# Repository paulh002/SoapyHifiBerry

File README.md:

# SoapyHifiBerry 
The SoapyHifiBerry driver is to use the HifiBerry DAC + ADC (Pro) as a SDR Tranceiver in combination with a Tayloe detector / Mixer.
The idea and design of the detector is from the book "Software Defined Radio Tranceiver" T41-EP by AC8GY and W8TEE
I adapted the design for use with Raspberry PI 4B. On the PCB there is a Tayloe mixer FST3253 / SN74CBT3252 and a Si5351 oscilator.
A SN74HC74 is used to devide the clock by 4 and deliver 90 degree phase shift. Alternative 2 si5351 can be used clock 0 and clock 1 will deliver 90 deg phase shift. A TCA9548 is used to switch the i2c bus.
The SoapyHifiBerry driver work with my SDR software SDRBERRY https://github.com/paulh002/sdrberry, I did not test it with other SDR software and all is an experiment.
(SoapyHifiBerry relies on RtAudio library, which is included staticly. This can give problems with applications using also RtAudio but a different version, 
in that case remove the RtAudio.cpp from SoapyHifiBerry and use correct RtAudio.h)

The sdr41-rxtx board uses a Si5351A-B-GM which has 8 outputs 2 outputs are used in quadrature for receive and 2 outputs for receive. Unfortunaly 160 M is not possible in this design because of limitations of the si5351.
An option would be to add a divide by 2 chip. The board compresses the whole design to a single pcb. SoapyHifiBerry can be configured by setting the mode to IQSINGLEMULTI and the multiplier to 1.

Done:
- Support 2 times Si5351 (RX and TX)
- Si5351 I2C interface
- Gain interface
- Receive IQ signal
- Transmit IQ interface
- CMake compilation

Installation of libraries is necessary:
- Liquid DSP
- Alsa audio
- SoapySDR
- pthread

# Installation

## Install libraries

git clone https://github.com/pothosware/SoapySDR.git
cd SoapySDR
git pull origin master
mkdir build
cd build
cmake ..
make -j4
sudo make install
sudo ldconfig

cd ~
sudo apt-get install -y fftw3-dev
git clone https://github.com/jgaeddert/liquid-dsp
git checkout v1.4.0
sudo apt-get install -y automake autoconf
cd liquid-dsp
./bootstrap.sh
./configure
make -j4
sudo make install
sudo ldconfig

## Install and compile with VisualStudio and VisualGDB
Download the repository in pi home directory  
```
git clone https://github.com/paulh002/SoapyHifiBerry  
Open project in VisualStudio and compile with VisualGDB

```

## Install and compile with CMake
```
git clone https://github.com/paulh002/SoapyHifiBerry  
cd SoapyHifiBerry
mkdir build
cd build
cmake ..
make
sudo make install
```

SoapyHifiBerry will create config file HifiBerry.cfg Si5351 correction can be configured and audio adc/dac alsa device name set
```
[si5351]
correction = "50000"
mode = "single"

[sound]
device = "snd_rpi_hifiberry_dacplusadcpro"
```

To enable 2 time si5351

```
[si5351]
mode = "IQ"
```

To enable single Si5351A-B-GM
```
[si5351]
correction = "121000"
correctiontx = "132500"
rxdrive = "2"
txdrive = "4"
mode = "IQSINGLEMULTI"
multiplier = 1
disabletxoutput = "on"
```

## QSD and QSE combined board (sdr41-rxtx)

## Separate QSD and QSE boards (Kicad rx and tx v3)

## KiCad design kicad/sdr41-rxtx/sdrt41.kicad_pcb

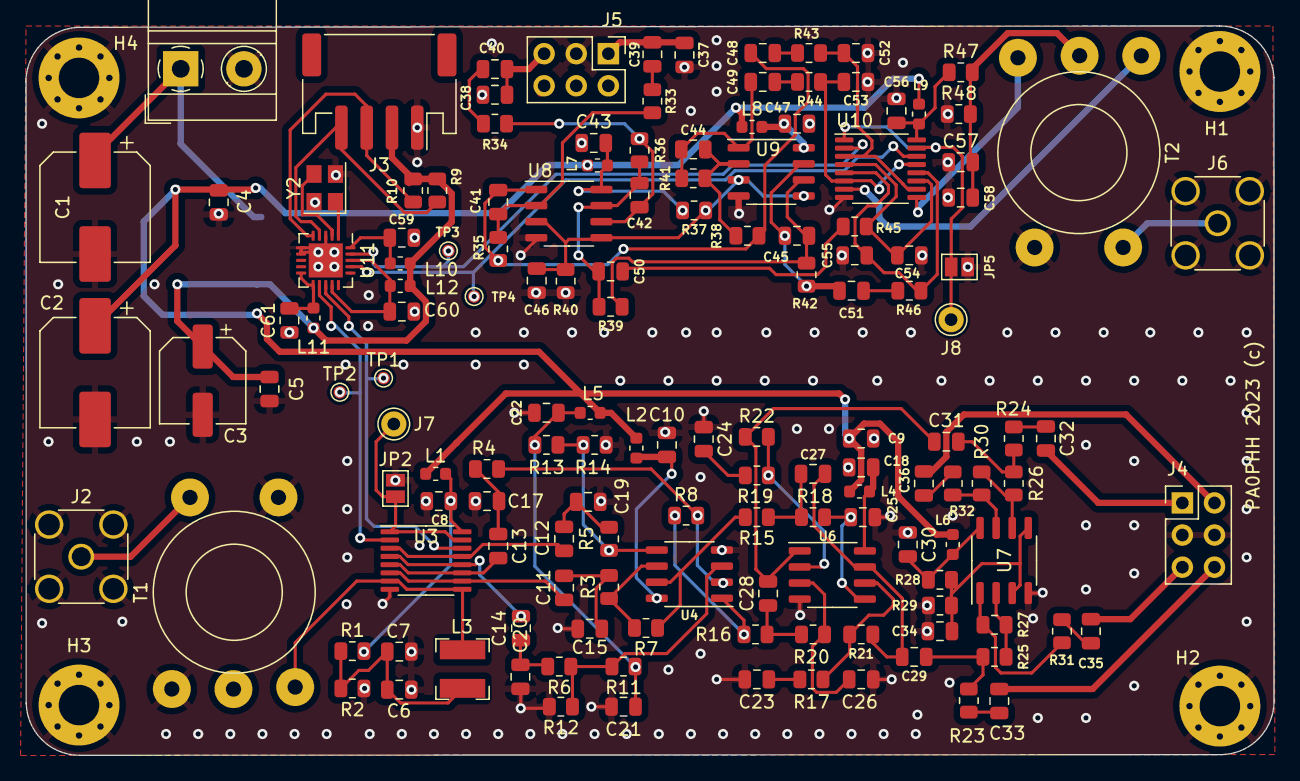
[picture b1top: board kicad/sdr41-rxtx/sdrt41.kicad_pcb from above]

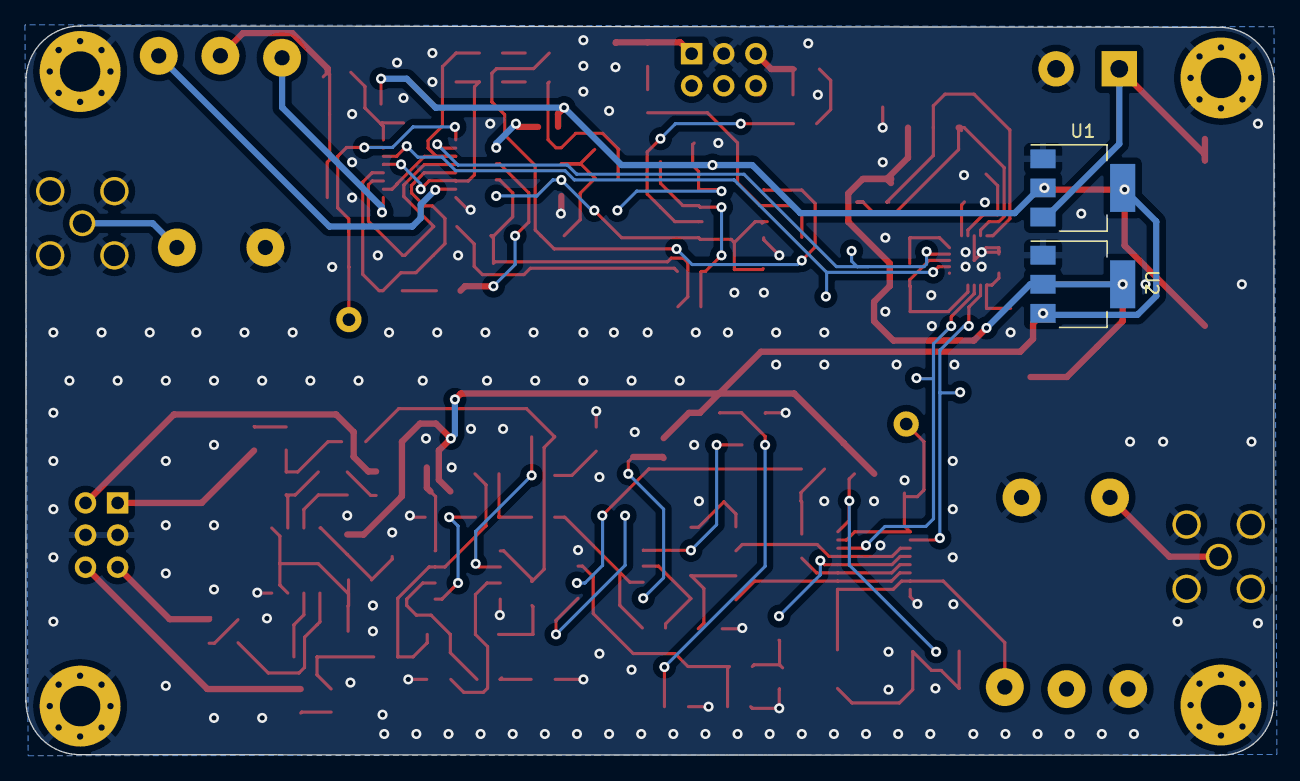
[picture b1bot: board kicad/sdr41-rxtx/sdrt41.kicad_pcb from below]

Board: 4 copper layers, 98.7 x 57.7 mm, 151 parts (2 on the bottom side), 92 nets.

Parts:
C1, C2: 100u; CP_Elec_8x10.5
C3: 47u; CP_Elec_6.3x7.7
C4, C5, C6, C8, C10, C18, C21, C22, C30, C34, C43, C47, C56, C57: 100n; C_0805_2012Metric
C7, C9, C23, C24, C29, C31, C32, C33, C35, C36, C39, C40, C46, C48, C49, C50, C51, C58, C59, C60, C61: 10u; C_0805_2012Metric
C11, C12, C13, C14: 1u; C_0805_2012Metric
C15, C17, C19, C20: 10n; C_0805_2012Metric
C25, C26, C27, C28: 68p; C_0805_2012Metric
C37, C38: 1n; C_0805_2012Metric
C41, C42, C44, C45: 100p; C_0805_2012Metric
C52, C53, C54, C55: 2n2; C_0805_2012Metric
H1, H2, H3, H4: MountingHole_Pad; MountingHole_3.2mm_M3_Pad_Via
J1: Power; TerminalBlock_MetzConnect_Type011_RT05502HBWC_1x02_P5.00mm_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
J2: Conn_Coaxial; SMA_Amphenol_132134_Vertical
J3: I2C; JST_PH_S4B-PH-SM4-TB_1x04-1MP_P2.00mm_Horizontal
J4: output; PinHeader_2x03_P2.54mm_Vertical
J5: input; PinHeader_2x03_P2.54mm_Vertical
J6: TX; SMA_Amphenol_132134_Vertical
J7: Rx; Pin_D1.0mm_L10.0mm
J8: Tx; Pin_D1.0mm_L10.0mm
JP2: RX; SolderJumper-2_P1.3mm_Open_Pad1.0x1.5mm
JP5: tx; SolderJumper-2_P1.3mm_Open_Pad1.0x1.5mm
L1, L2, L4, L5, L6, L7, L8, L9, L10, L11, L12: L; L_0603_1608Metric
L3: 100u; L_Bourns-SRN4018
R1, R2, R7, R8: 2k; R_0805_2012Metric
R3, R4, R5, R6, R23, R24, R31, R32: 100; R_0805_2012Metric
R9, R10, R37, R40, R47, R48: 2k2; R_0805_2012Metric
R11, R12, R13, R14, R28, R29, R33, R34, R35, R36, R38, R39, R41, R42: 10k; R_0805_2012Metric
R15, R16, R17, R18, R19, R20, R21, R22, R27, R30: 5.1k; R_0805_2012Metric
R25, R26: 5k1; R_0805_2012Metric
R43, R44, R45, R46: 50; R_0805_2012Metric
T1: 1:4; Transformer_Toroid_Horizontal_D12.5mm_Amidon-T44
T2: 4:1; Transformer_Toroid_Horizontal_D12.5mm_Amidon-T44
TP1: Tp1; TestPoint_Pad_D1.0mm
TP2: Tp2; TestPoint_Pad_D1.0mm
TP3: Tp3; TestPoint_Pad_D1.0mm
TP4: Tp4; TestPoint_Pad_D1.0mm
U1: LM1117-5.0; SOT-223-3_TabPin2
U2: LM1117-3.3; SOT-223-3_TabPin2
U3, U10: SN74CBT3253; TSSOP-16_4.4x5mm_P0.65mm
U4, U6, U7, U8, U9: MC33078; SO-8_3.9x4.9mm_P1.27mm
U11: Si5351A-B-GM; QFN-20-1EP_4x4mm_P0.5mm_EP2.7x2.7mm
Y2: 25 Mhz; Crystal_SMD_3225-4Pin_3.2x2.5mm

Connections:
+3V3: C3.1, C5.2, J3.2, L10.1, L11.1, L12.1, R9.1, R10.1, U2.2 (VO)
+5V: C2.1, C4.2, C9.1, L1.1, L2.1, L4.1, L5.1, L6.1, L7.1, L8.1, L9.1, U1.2 (VO), U2.3 (VI)
+12C: C10.2, L2.2, U4.8 (V+)
+12P: C18.2, L4.2, U6.8 (V+)
+12V: C1.1, J1.1, U1.3 (VI)
/I+: C33.2, J4.6
/I-: C35.1, J4.5
/Q+: C32.2, J4.1
/Q-: C36.2, J4.2
/QSE/I-tx: C37.2, C39.1, J5.1
/QSE/Q-tx: C38.2, C40.1, J5.5
Clock1: TP1.1, U3.14 (S0), U11.13 (CLK0)
Clock2: TP2.1, U3.2 (S1), U11.12 (CLK1)
Clock3: TP3.1, U10.2 (S1), U11.19 (CLK4)
Clock4: TP4.1, U10.14 (S0), U11.17 (CLK5)
GND: C1.2, C2.2, C3.2, C4.1, C5.1, C6.1, C7.1, C8.1, C9.2, C10.1, C15.1, C17.1, C18.1, C19.1, C20.1, C21.1, C22.1, C23.1, C24.1, C25.1, C26.1, C30.1, C34.1, C37.1, C38.1, C43.1, C46.1, C47.1, C52.1, C53.1, C54.1, C55.1, C56.1, C57.1, C58.1, C59.1, C60.1, C61.1, H1.1, H2.1, H3.1, H4.1, J1.2, J2.2 (Ext), J3.1, J4.3, J4.4, J5.3, J6.2 (Ext), JP2.1 (A), JP5.1 (A), R2.2, R12.2, R14.2, R29.2, R40.1, R48.1, T1.1 (AA), T1.3 (SA), T2.1 (AA), U1.1 (GND), U2.1 (GND), U3.8 (GND), U4.4 (V-), U6.4 (V-), U7.4 (V-), U8.4 (V-), U9.4 (V-), U10.8 (GND), U11.3 (A0), U11.6 (SSEN), U11.7 (OEB), U11.21 (GND), Y2.2, Y2.4
unnamed: C6.2, C7.2, L3.2, R1.1, R2.1
unnamed: C11.1, C15.2, R3.2
unnamed: C12.1, C19.2, R5.2
unnamed: C13.1, C17.2, R4.2
unnamed: C14.1, C20.2, R6.2
unnamed: C21.2, C22.2, L5.2, R11.1, R13.1
unnamed: C23.2, R17.1
unnamed: C24.2, R19.1
unnamed: C27.1, R15.1, R18.2
unnamed: C27.2, C29.1, R21.1, U6.7
unnamed: C28.1, R16.1, R20.2
unnamed: C28.2, C31.1, R22.1, U6.1
unnamed: C29.2, R23.2, R25.2
unnamed: C31.2, R24.2, R26.2
unnamed: C32.1, R24.1
unnamed: C33.1, R23.1
unnamed: C35.2, R31.1
unnamed: C36.1, R32.1
unnamed: C39.2, R33.1
unnamed: C40.2, R34.1
unnamed: C41.1, C48.1, R35.2, R38.1, U8.1
unnamed: C42.1, C50.1, R36.2, R39.1, U8.7
unnamed: C44.1, C49.1, R41.2, U9.1
unnamed: C45.1, C51.1, R42.2, U9.7
unnamed: C48.2, R43.1
unnamed: C49.2, R44.1
unnamed: C50.2, R45.1
unnamed: C51.2, R46.1
unnamed: J2.1 (In), T1.2 (AB)
unnamed: J6.1 (In), T2.2 (AB)
unnamed: J7.1, JP2.2 (B), U3.1 (1~OE), U3.15 (2~OE)
unnamed: J8.1, JP5.2 (B), U10.1 (1~OE), U10.15 (2~OE)
unnamed: R7.1, R15.2, U4.7
unnamed: R8.1, R16.2, U4.1
unnamed: R27.1, R31.2, U7.1
unnamed: R30.1, R32.2, U7.7
unnamed: L3.1, T1.5 (SB), U3.7 (1A), U3.9 (2A)
unnamed: T2.3 (SA), U10.7 (1A)
unnamed: T2.5 (SB), U10.9 (2A)
unnamed: C57.2, C58.2, R47.2, R48.2, T2.4 (SC)
unnamed: C11.2, U3.6 (1B1), U3.10 (2B1)
unnamed: C13.2, U3.5 (1B2), U3.11 (2B2)
unnamed: C14.2, U3.4 (1B3), U3.12 (2B3)
unnamed: C12.2, U3.3 (1B4), U3.13 (2B4)
unnamed: C8.2, L1.2, R1.2, U3.16 (VCC)
unnamed: R6.1, R11.2, R12.1, U4.3 (+)
unnamed: R4.1, R8.2, U4.2 (-)
unnamed: R5.1, R13.2, R14.1, U4.5 (+)
unnamed: R3.1, R7.2, U4.6 (-)
unnamed: C26.2, R20.1, U6.3 (+)
unnamed: R19.2, R22.2, U6.2 (-)
unnamed: C25.2, R18.1, U6.5 (+)
unnamed: R17.2, R21.2, U6.6 (-)
unnamed: R25.1, R27.2, U7.2 (-)
unnamed: R26.1, R30.2, U7.6 (-)
unnamed: C30.2, L6.2, R28.1, U7.8 (V+)
unnamed: C46.2, R37.2, R40.2, U8.3 (+), U8.5 (+), U9.3 (+), U9.5 (+)
unnamed: C41.2, R33.2, R35.1, U8.2 (-)
unnamed: C42.2, R34.2, R36.1, U8.6 (-)
unnamed: C43.2, L7.2, R37.1, U8.8 (V+)
unnamed: C44.2, R38.2, R41.1, U9.2 (-)
unnamed: C45.2, R39.2, R42.1, U9.6 (-)
unnamed: C47.2, L8.2, U9.8 (V+)
unnamed: C53.2, R44.2, U10.6 (1B1), U10.13 (2B4)
unnamed: C55.2, R46.2, U10.5 (1B2), U10.12 (2B3)
unnamed: C54.2, R45.2, U10.4 (1B3), U10.11 (2B2)
unnamed: C52.2, R43.2, U10.3 (1B4), U10.10 (2B1)
unnamed: C56.2, L9.2, R47.1, U10.16 (VCC)
unnamed: C59.2, L10.2, U11.20 (VDD)
unnamed: C61.2, L11.2, U11.10 (VDDOB), U11.11 (VDDOA)
unnamed: C60.2, L12.2, U11.14 (VDDOD), U11.18 (VDDOC)
unnamed: U11.1 (XA), Y2.1
unnamed: U11.2 (XB), Y2.3
SCL: J3.4, R9.2, U11.4 (SCL)
SDA: J3.3, R10.2, U11.5 (SDA)
Vbal: C34.2, R28.2, R29.1, U7.3 (+), U7.5 (+)

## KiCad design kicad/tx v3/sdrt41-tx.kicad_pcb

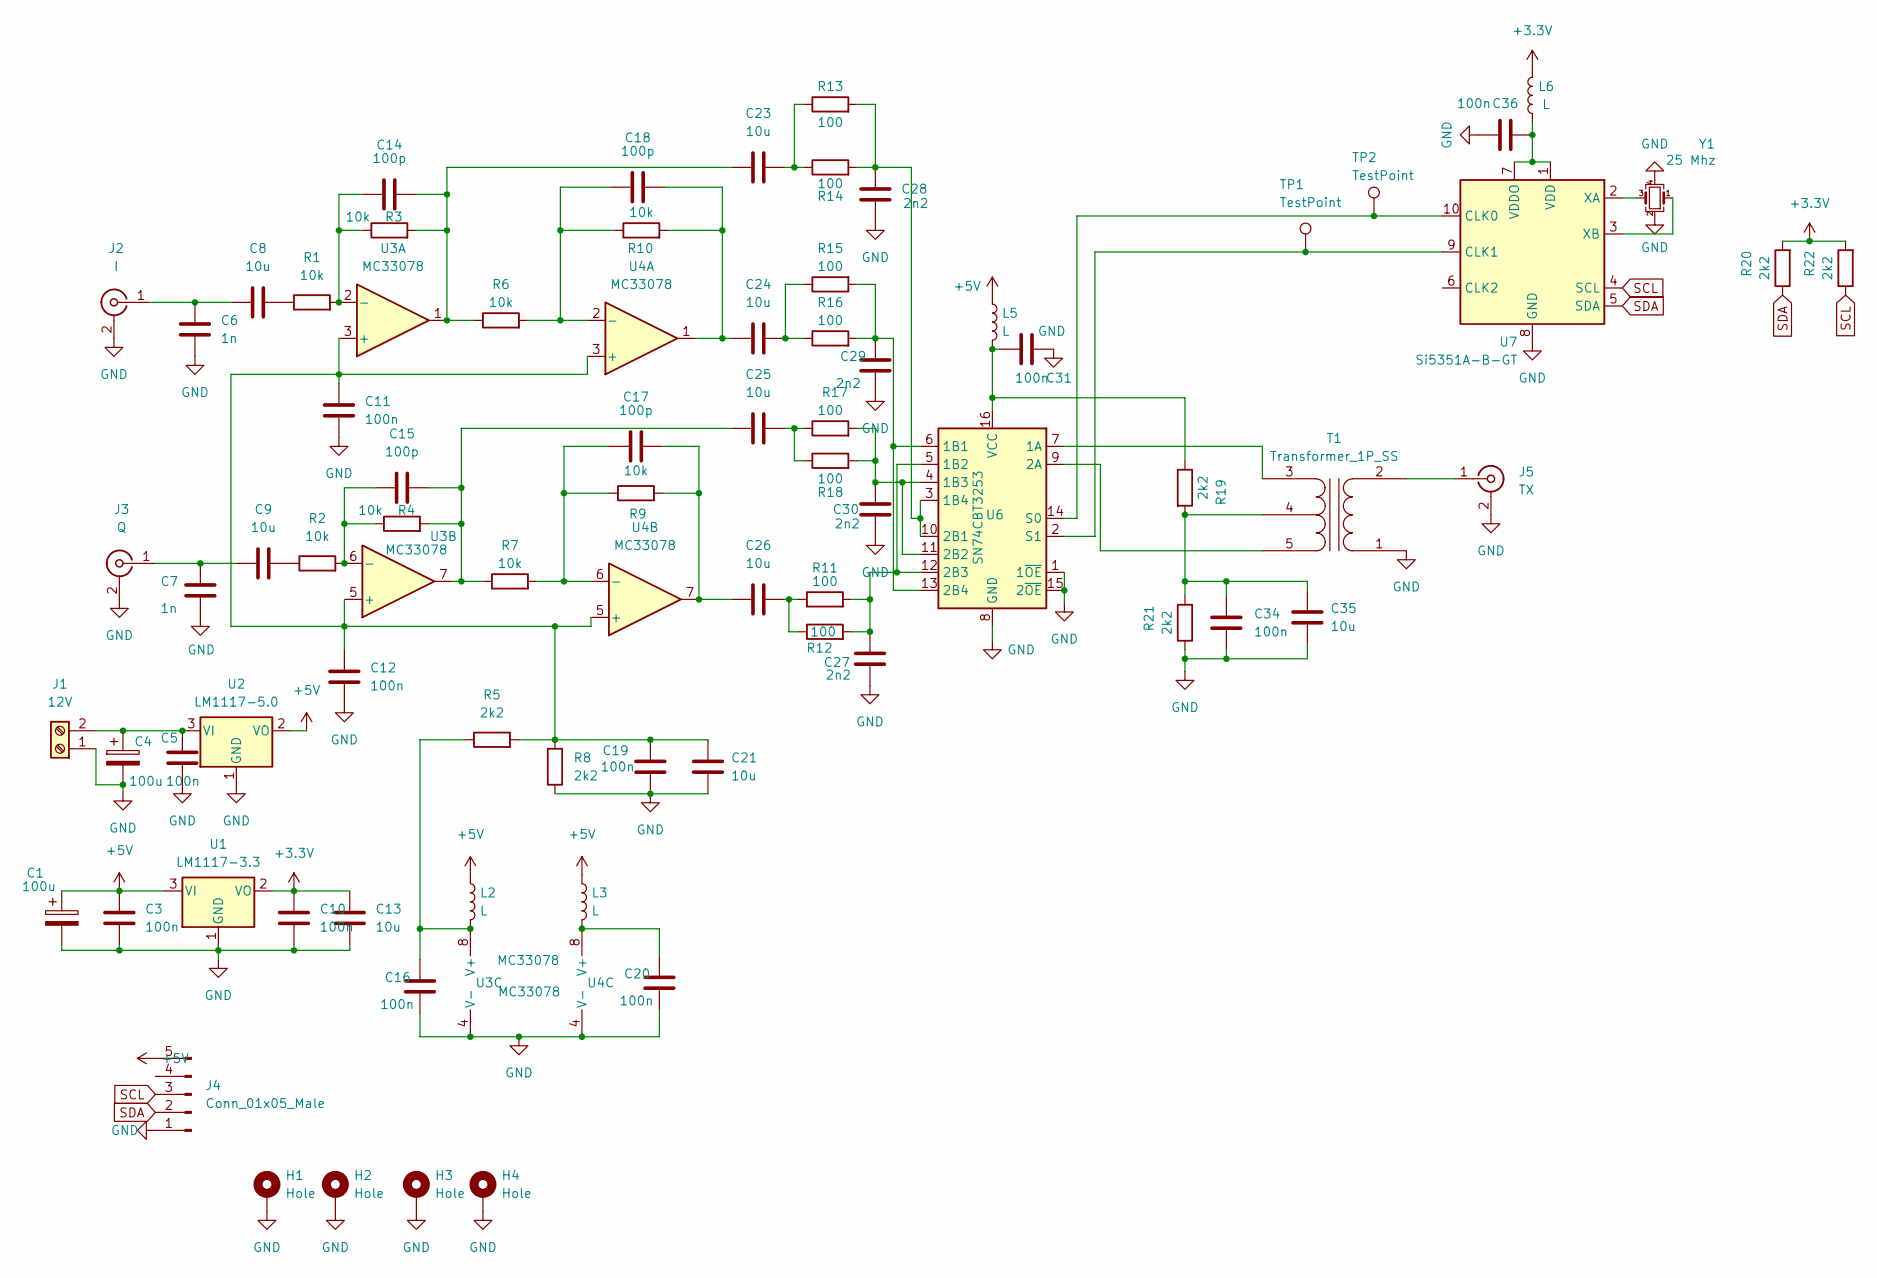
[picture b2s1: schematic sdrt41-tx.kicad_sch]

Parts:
C1, C4: 100u; C_Radial_D5.0mm_H7.0mm_P2.00mm
C3, C5, C10, C11, C12, C16, C19, C20, C31, C34, C36: 100n; C_0805_2012Metric
C6, C7: 1n; C_0805_2012Metric
C8, C9, C21, C23, C24, C25, C26, C35: 10u; C_1206_3216Metric
C13: 10u; C_0805_2012Metric
C14, C15, C17, C18: 100p; C_0805_2012Metric
C27, C28, C29, C30: 2n2; C_0805_2012Metric
H1, H2, H3, H4: Hole; MountingHole_3.2mm_M3_Pad_Via
J1: 12V; TerminalBlock_MetzConnect_Type011_RT05502HBWC_1x02_P5.00mm_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
J2: I; SMA_Amphenol_132134_Vertical
J3: Q; SMA_Amphenol_132134_Vertical
J4: Conn_01x05_Male; PinHeader_1x05_P2.54mm_Vertical
J5: TX; SMA_Amphenol_132134_Vertical
L2, L3, L5, L6: L; L_0603_1608Metric
R1, R2, R3, R4, R6, R7, R9, R10: 10k; R_0805_2012Metric
R5, R8, R19, R20, R21, R22: 2k2; R_0805_2012Metric
R11, R12, R13, R14, R15, R16, R17, R18: 100; R_0805_2012Metric
T1: Transformer_1P_SS; Transformer_Toroid_Horizontal_D12.5mm_Amidon-T44
TP1, TP2: TestPoint; TestPoint_Pad_D1.0mm
U1: LM1117-3.3; SOT-223-3_TabPin2
U2: LM1117-5.0; SOT-223-3_TabPin2
U3, U4: MC33078; SO-8_3.9x4.9mm_P1.27mm
U6: SN74CBT3253; TSSOP-16_4.4x5mm_P0.65mm
U7: Si5351A-B-GT; MSOP-10_3x3mm_P0.5mm
Y1: 25 Mhz; Crystal_SMD_3225-4Pin_3.2x2.5mm

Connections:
+3.3V: C10.2, C13.2, L6.1, R20.2, R22.2, U1.2 (VO)
+5V: C1.1, C3.2, J4.5, L2.1, L3.1, L5.1, U1.3 (VI), U2.2 (VO)
GND: C1.2, C3.1, C4.2, C5.1, C6.1, C7.1, C10.1, C11.1, C12.1, C13.1, C16.1, C19.1, C20.1, C21.1, C27.1, C28.1, C29.1, C30.1, C31.1, C34.1, C35.1, C36.1, H1.1, H2.1, H3.1, H4.1, J1.1, J2.2 (Ext), J3.2 (Ext), J4.1, J5.2 (Ext), R8.1, R21.1, T1.1 (AA), U1.1 (GND), U2.1 (GND), U3.4 (V-), U4.4 (V-), U6.1 (1~OE), U6.8 (GND), U6.15 (2~OE), U7.8 (GND), Y1.2, Y1.4
unnamed: C8.2, R1.1
unnamed: C9.2, R2.1
unnamed: C14.1, C23.1, R3.2, R6.1, U3.1
unnamed: C15.1, C25.1, R4.2, R7.1, U3.7
unnamed: C17.1, C26.1, R9.2, U4.7
unnamed: C18.1, C24.1, R10.2, U4.1
unnamed: C23.2, R13.1, R14.1
unnamed: C24.2, R15.1, R16.1
unnamed: C25.2, R17.1, R18.1
unnamed: C26.2, R11.1, R12.1
unnamed: C4.1, C5.2, J1.2, U2.3 (VI)
unnamed: C6.2, C8.1, J2.1 (In)
unnamed: C7.2, C9.1, J3.1 (In)
unnamed: J5.1 (In), T1.2 (AB)
unnamed: T1.3 (SA), U6.7 (1A)
unnamed: T1.5 (SB), U6.9 (2A)
unnamed: C34.2, C35.2, R19.2, R21.2, T1.4 (SC)
unnamed: C11.2, C12.2, C19.2, C21.2, R5.2, R8.2, U3.3 (+), U3.5 (+), U4.3 (+), U4.5 (+)
unnamed: C14.2, R1.2, R3.1, U3.2 (-)
unnamed: C15.2, R2.2, R4.1, U3.6 (-)
unnamed: C16.2, L2.2, R5.1, U3.8 (V+)
unnamed: C18.2, R6.2, R10.1, U4.2 (-)
unnamed: C17.2, R7.2, R9.1, U4.6 (-)
unnamed: C20.2, L3.2, U4.8 (V+)
unnamed: C29.2, R15.2, R16.2, U6.6 (1B1), U6.13 (2B4)
unnamed: C27.2, R11.2, R12.2, U6.5 (1B2), U6.12 (2B3)
unnamed: C30.2, R17.2, R18.2, U6.4 (1B3), U6.11 (2B2)
unnamed: C28.2, R13.2, R14.2, U6.3 (1B4), U6.10 (2B1)
unnamed: TP2.1, U6.14 (S0), U7.10 (CLK0)
unnamed: TP1.1, U6.2 (S1), U7.9 (CLK1)
unnamed: C31.2, L5.2, R19.1, U6.16 (VCC)
unnamed: C36.2, L6.2, U7.1 (VDD), U7.7 (VDDO)
unnamed: U7.2 (XA), Y1.3
unnamed: U7.3 (XB), Y1.1
SCL: J4.3, R22.1, U7.4 (SCL)
SDA: J4.2, R20.1, U7.5 (SDA)

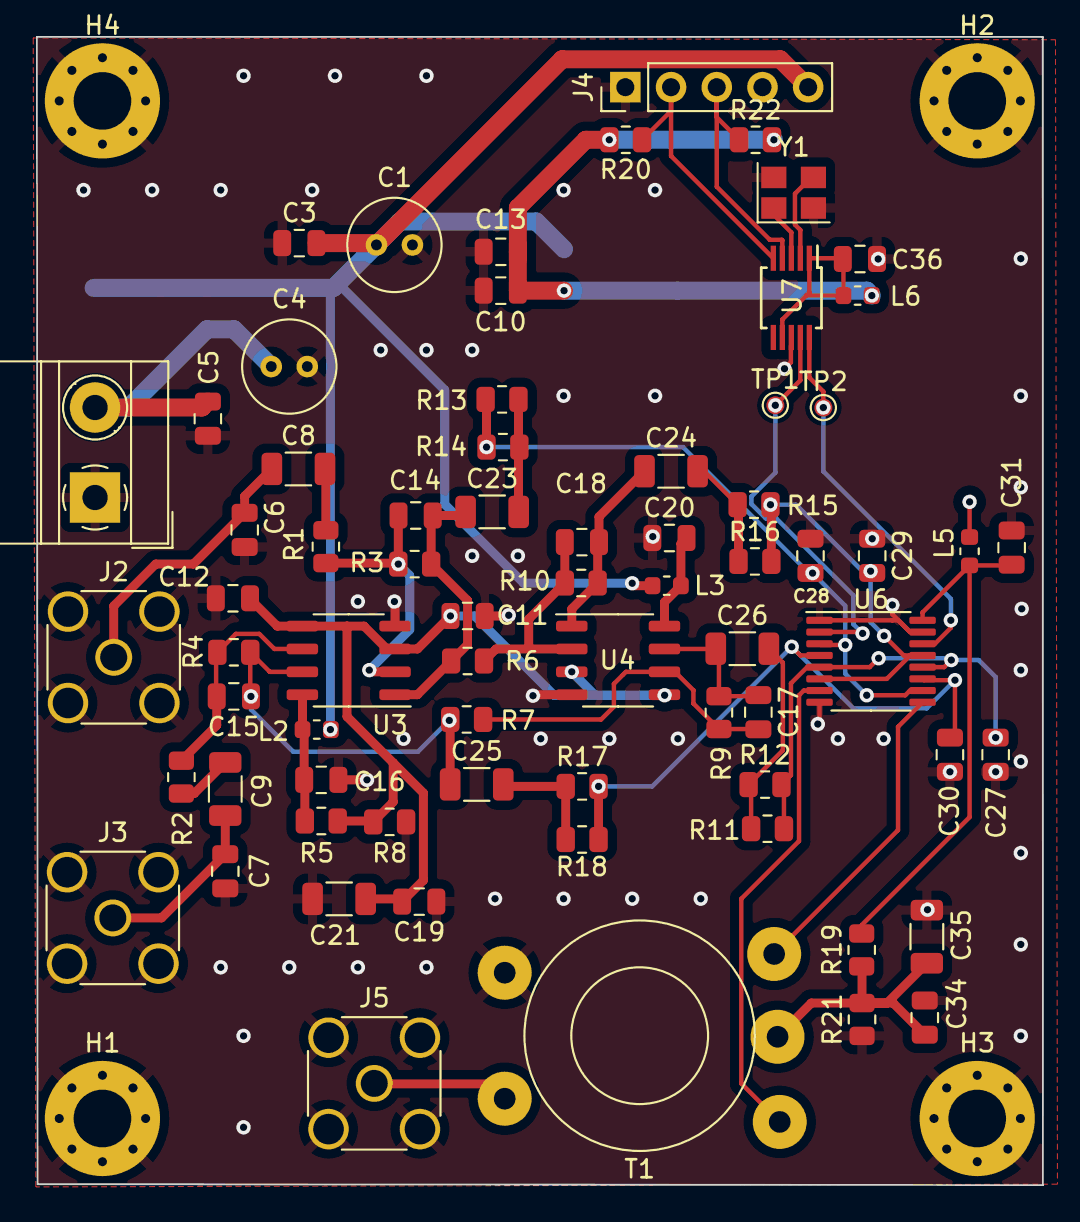
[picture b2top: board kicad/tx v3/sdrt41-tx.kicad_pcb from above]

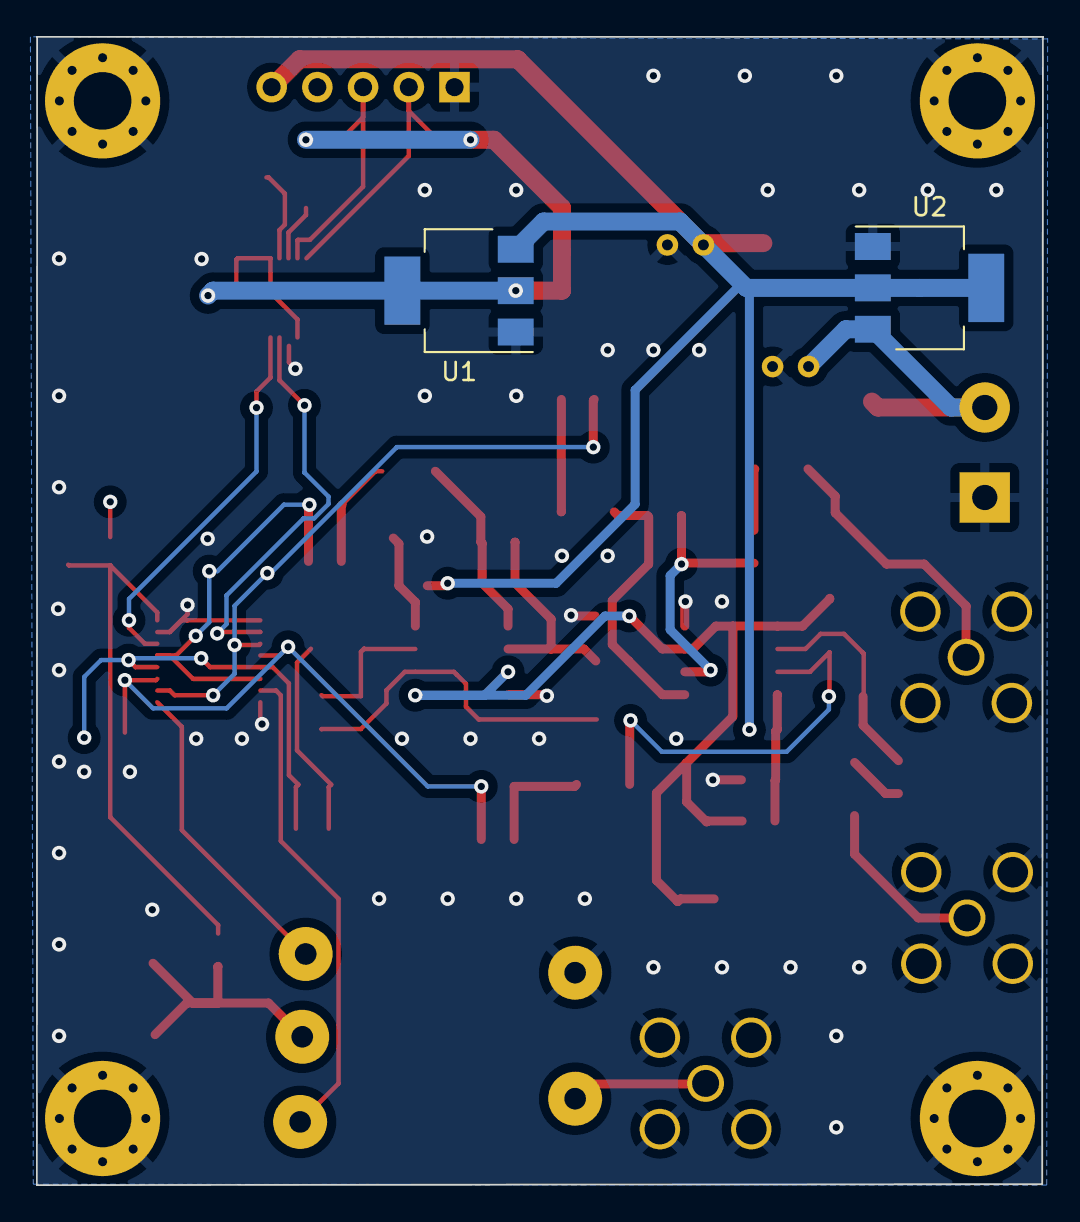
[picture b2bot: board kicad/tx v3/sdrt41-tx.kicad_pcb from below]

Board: 4 copper layers, 55.9 x 63.8 mm, 77 parts (2 on the bottom side), 39 nets.

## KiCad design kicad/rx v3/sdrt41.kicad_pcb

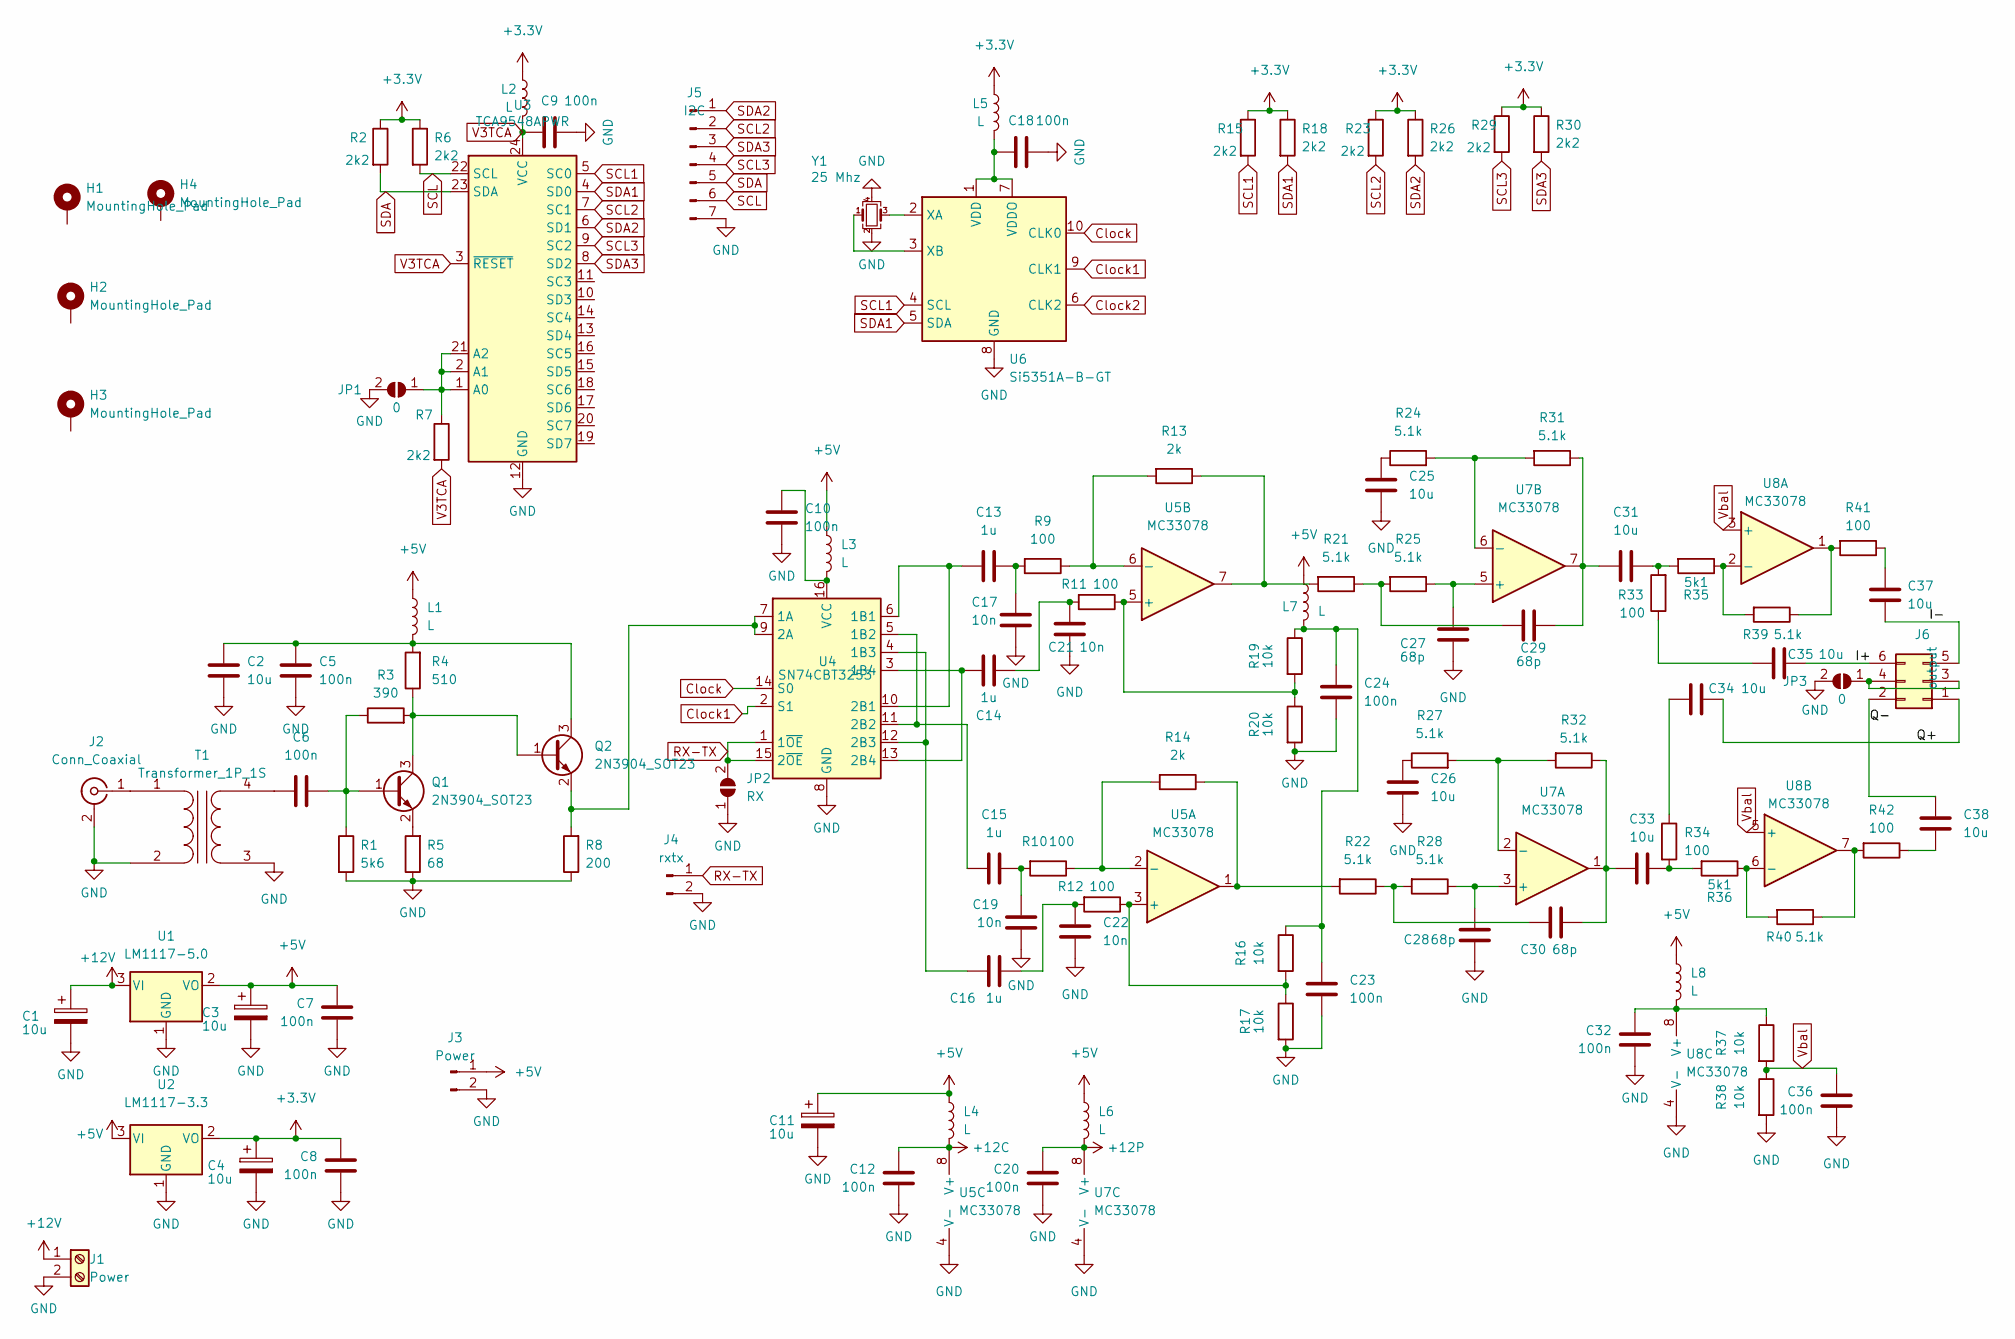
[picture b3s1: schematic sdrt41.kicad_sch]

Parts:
C1, C3: 10u; C_Radial_D10.0mm_H12.5mm_P5.00mm
C2, C11, C25, C26: 10u; C_1206_3216Metric
C4: 10u; C_Radial_D6.3mm_H5.0mm_P2.50mm
C5, C6, C7, C8, C9, C10, C12, C18, C20, C23, C24, C32, C36: 100n; C_0805_2012Metric
C13, C14, C15, C16: 1u; C_0805_2012Metric
C17, C19, C21, C22: 10n; C_0805_2012Metric
C27, C28, C29, C30: 68p; C_0805_2012Metric
C31, C33, C34, C35, C37, C38: 10u; C_0805_2012Metric
H1, H2, H3, H4: MountingHole_Pad; MountingHole_3.2mm_M3_Pad_Via
J1: Power; TerminalBlock_MetzConnect_Type011_RT05502HBWC_1x02_P5.00mm_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
J2: Conn_Coaxial; SMA_Amphenol_132134_Vertical
J3: Power; PinHeader_1x02_P2.54mm_Vertical
J4: rxtx; PinHeader_1x02_P2.54mm_Vertical
J5: I2C; PinHeader_1x07_P2.54mm_Vertical
J6: output; PinHeader_2x03_P2.54mm_Vertical
JP1, JP3: 0; SolderJumper-2_P1.3mm_Open_Pad1.0x1.5mm
JP2: RX; SolderJumper-2_P1.3mm_Open_Pad1.0x1.5mm
L1, L2, L3, L4, L5, L6, L7, L8: L; L_0603_1608Metric
Q1, Q2: 2N3904_SOT23; SOT-23
R1: 5k6; R_0805_2012Metric
R2, R6, R7, R15, R18, R23, R26, R29, R30: 2k2; R_0805_2012Metric
R3: 390; R_0805_2012Metric
R4: 510; R_0805_2012Metric
R5: 68; R_0805_2012Metric
R8: 200; R_0805_2012Metric
R9, R10, R11, R12, R33, R34, R41, R42: 100; R_0805_2012Metric
R13, R14: 2k; R_0805_2012Metric
R16, R17, R19, R20, R37, R38: 10k; R_0805_2012Metric
R21, R22, R24, R25, R27, R28, R31, R32, R39, R40: 5.1k; R_0805_2012Metric
R35, R36: 5k1; R_0805_2012Metric
T1: Transformer_1P_1S; Transformer_Toroid_Horizontal_D14.0mm_Amidon-T50
U1: LM1117-5.0; SOT-223-3_TabPin2
U2: LM1117-3.3; SOT-223-3_TabPin2
U3: TCA9548APWR; TSSOP-24_4.4x7.8mm_P0.65mm
U4: SN74CBT3253; TSSOP-16_4.4x5mm_P0.65mm
U5, U7, U8: MC33078; SO-8_3.9x4.9mm_P1.27mm
U6: Si5351A-B-GT; MSOP-10_3x3mm_P0.5mm
Y1: 25 Mhz; Crystal_SMD_3225-4Pin_3.2x2.5mm

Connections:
+3V3: C4.1, C8.2, L2.1, L5.1, R2.1, R6.1, R15.1, R18.1, R23.1, R26.1, R29.1, R30.1, U2.2 (VO)
+5V: C3.1, C7.2, C11.1, J3.1, L1.1, L3.1, L4.1, L6.1, L7.1, L8.1, U1.2 (VO), U2.3 (VI)
+12C: C12.2, L4.2, U5.8 (V+)
+12P: C20.2, L6.2, U7.8 (V+)
+12V: C1.1, J1.1, U1.3 (VI)
/I+: C35.2, J6.6
/I-: C37.1, J6.5
/Q+: C34.2, J6.1
/Q-: C38.2, J6.2
Clock: U4.14 (S0), U6.10 (CLK0)
Clock1: U4.2 (S1), U6.9 (CLK1)
Clock2: U6.6 (CLK2)
GND: C1.2, C2.1, C3.2, C4.2, C5.1, C7.1, C8.1, C9.1, C10.1, C11.2, C12.1, C17.1, C18.1, C19.1, C20.1, C21.1, C22.1, C23.1, C24.1, C25.1, C26.1, C27.1, C28.1, C32.1, C36.1, J1.2, J2.2 (Ext), J3.2, J4.2, J5.7, JP1.2 (B), JP2.1 (A), JP3.2 (B), R1.2, R5.1, R8.1, R17.2, R20.2, R38.2, T1.2 (AB), T1.3 (SA), U1.1 (GND), U2.1 (GND), U3.12 (GND), U4.8 (GND), U5.4 (V-), U6.8 (GND), U7.4 (V-), U8.4 (V-), Y1.2, Y1.4
unnamed: C2.2, C5.2, L1.2, Q2.3 (C), R4.2
unnamed: C6.1, T1.4 (SB)
unnamed: C6.2, Q1.1 (B), R1.1, R3.1
unnamed: C10.2, L3.2, U4.16 (VCC)
unnamed: C13.1, C17.2, R9.2
unnamed: C13.2, U4.6 (1B1), U4.10 (2B1)
unnamed: C14.1, C21.2, R11.2
unnamed: C14.2, U4.3 (1B4), U4.13 (2B4)
unnamed: C15.1, C19.2, R10.2
unnamed: C15.2, U4.5 (1B2), U4.11 (2B2)
unnamed: C16.1, C22.2, R12.2
unnamed: C16.2, U4.4 (1B3), U4.12 (2B3)
unnamed: C18.2, L5.2, U6.1 (VDD), U6.7 (VDDO)
unnamed: C23.2, C24.2, L7.2, R16.1, R19.1
unnamed: C25.2, R24.1
unnamed: C26.2, R27.1
unnamed: C27.2, R25.1, U7.5 (+)
unnamed: C28.2, R28.1, U7.3 (+)
unnamed: C29.1, R21.1, R25.2
unnamed: C29.2, C31.1, R31.1, U7.7
unnamed: C30.1, R22.1, R28.2
unnamed: C30.2, C33.1, R32.1, U7.1
unnamed: C31.2, R33.2, R35.2
unnamed: C32.2, L8.2, R37.1, U8.8 (V+)
unnamed: C33.2, R34.2, R36.2
unnamed: C34.1, R34.1
unnamed: C35.1, R33.1
unnamed: C37.2, R41.1
unnamed: C38.1, R42.1
unnamed: J2.1 (In), T1.1 (AA)
unnamed: J6.3, J6.4, JP3.1 (A)
unnamed: JP1.1 (A), R7.1, U3.1 (A0), U3.2 (A1), U3.21 (A2)
unnamed: Q1.2 (E), R5.2
unnamed: Q1.3 (C), Q2.1 (B), R3.2, R4.1
unnamed: Q2.2 (E), R8.2, U4.7 (1A), U4.9 (2A)
unnamed: R10.1, R14.2, U5.2 (-)
unnamed: R11.1, R19.2, R20.1, U5.5 (+)
unnamed: R12.1, R16.2, R17.1, U5.3 (+)
unnamed: R13.1, R21.2, U5.7
unnamed: R9.1, R13.2, U5.6 (-)
unnamed: R14.1, R22.2, U5.1
unnamed: R24.2, R31.2, U7.6 (-)
unnamed: R27.2, R32.2, U7.2 (-)
unnamed: R35.1, R39.2, U8.2 (-)
unnamed: R36.1, R40.2, U8.6 (-)
unnamed: R39.1, R41.2, U8.1
unnamed: R40.1, R42.2, U8.7
unnamed: U6.2 (XA), Y1.3
unnamed: U6.3 (XB), Y1.1
RX-TX: J4.1, JP2.2 (B), U4.1 (1~OE), U4.15 (2~OE)
SCL: J5.6, R6.2, U3.22 (SCL)
SCL1: R15.2, U3.5 (SC0), U6.4 (SCL)
SCL2: J5.2, R23.2, U3.7 (SC1)
SCL3: J5.4, R29.2, U3.9 (SC2)
SDA: J5.5, R2.2, U3.23 (SDA)
SDA1: R18.2, U3.4 (SD0), U6.5 (SDA)
SDA2: J5.1, R26.2, U3.6 (SD1)
SDA3: J5.3, R30.2, U3.8 (SD2)
V3TCA: C9.2, L2.2, R7.2, U3.3 (~RESET), U3.24 (VCC)
Vbal: C36.2, R37.2, R38.1, U8.3 (+), U8.5 (+)

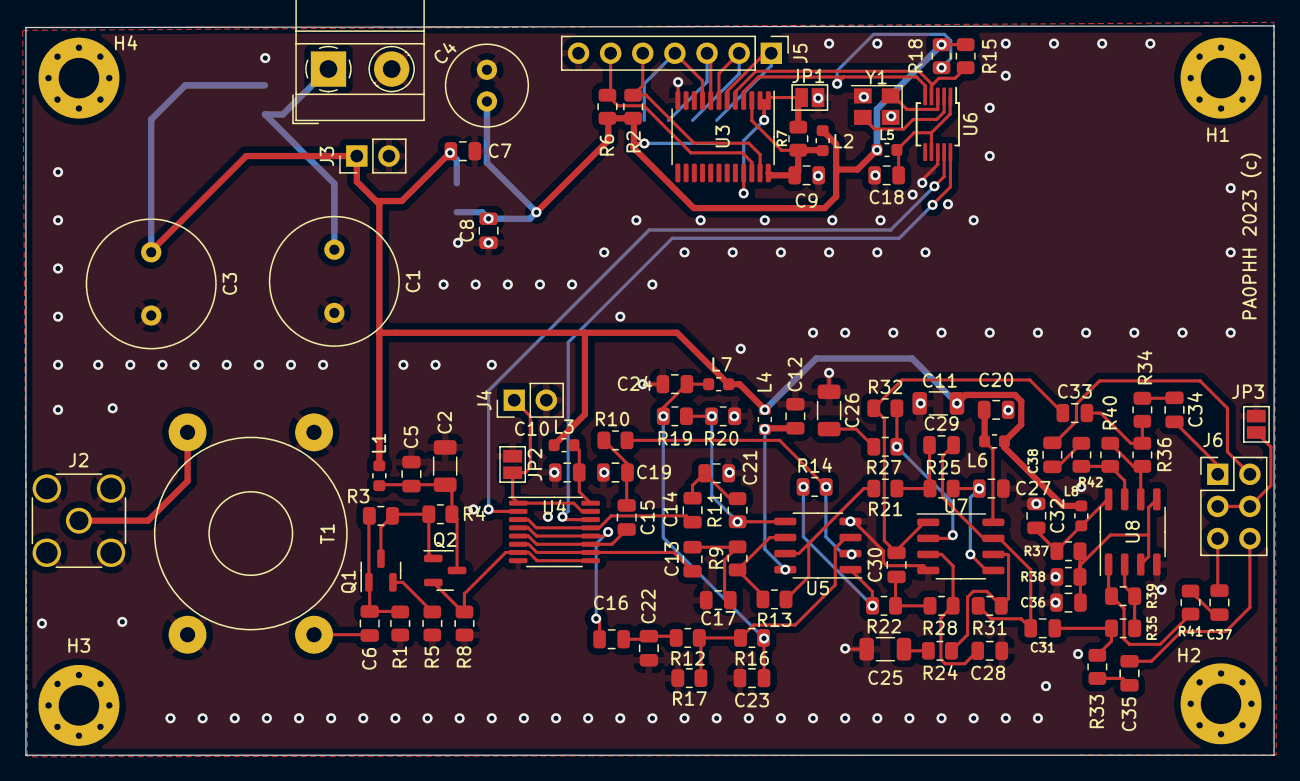
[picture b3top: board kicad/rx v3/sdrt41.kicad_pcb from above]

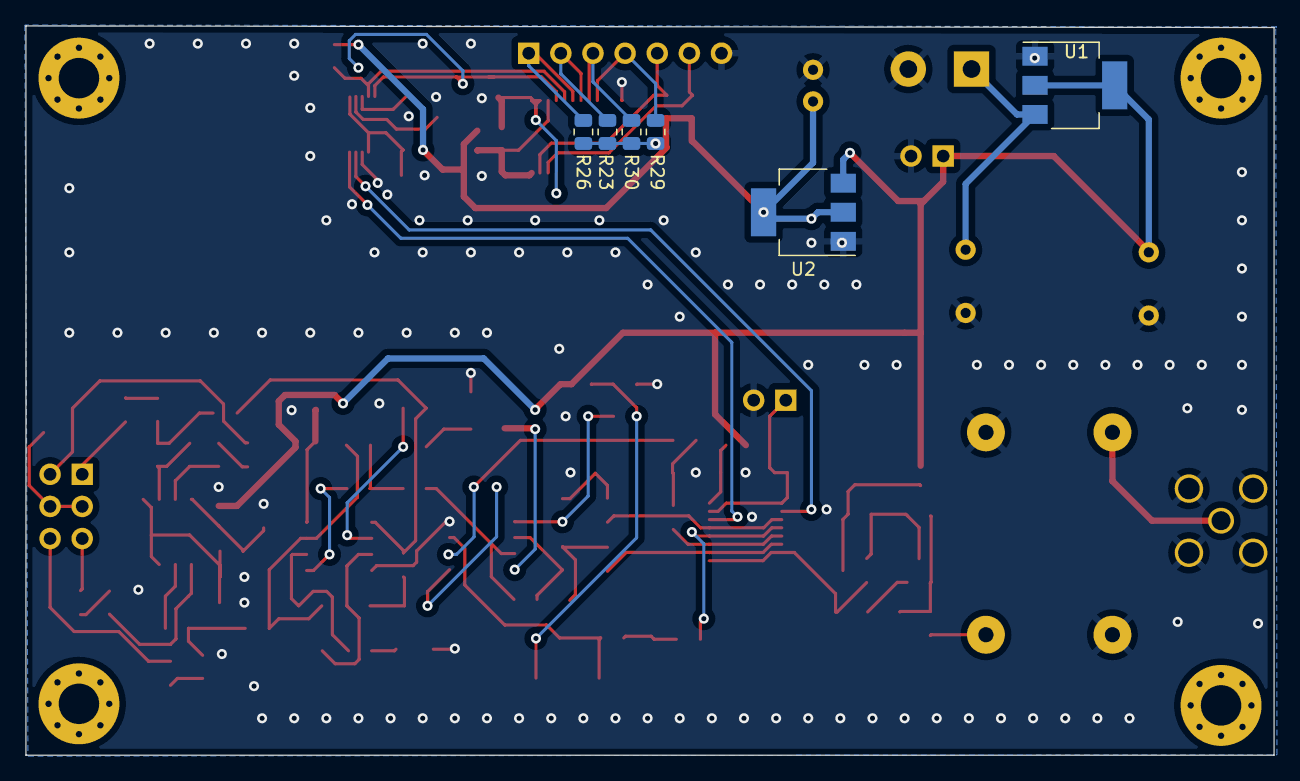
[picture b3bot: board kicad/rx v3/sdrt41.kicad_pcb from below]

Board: 4 copper layers, 98.7 x 57.7 mm, 113 parts (6 on the bottom side), 72 nets.
